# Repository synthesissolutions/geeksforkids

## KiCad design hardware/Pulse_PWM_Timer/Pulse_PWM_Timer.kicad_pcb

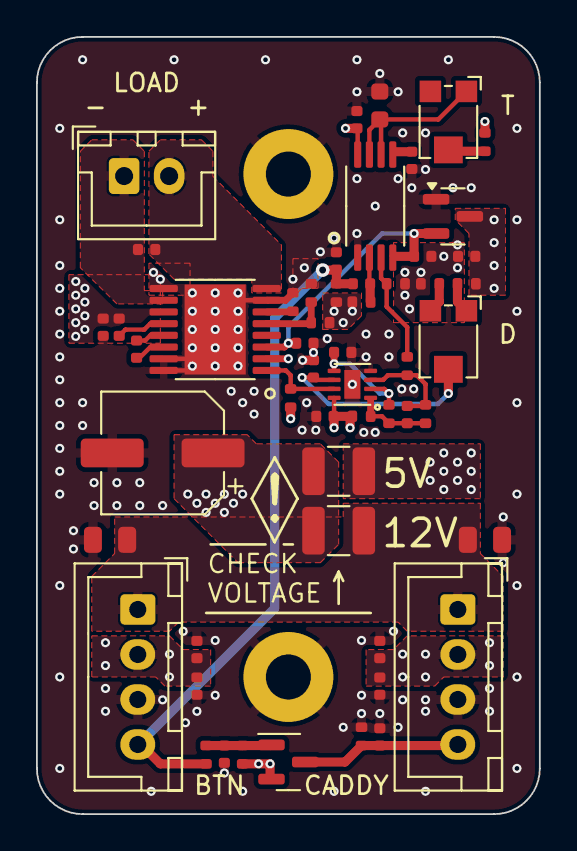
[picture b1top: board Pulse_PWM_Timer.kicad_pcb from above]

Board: 4 copper layers, 27.9 x 43.2 mm, 56 parts (0 on the bottom side), 27 nets.

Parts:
C1, C2, C3, C5, C9, C12, C16, C19, C21, C23, C25: 100nF; C_0402_1005Metric
C4, C10, C11, C17, C20: 10nF; C_0402_1005Metric
C6, C14: 22uF; C_0805_2012Metric
C7, C8, C15: 1uF; C_0402_1005Metric
C13: 10uF; C_0603_1608Metric
C18, C22: 22nF; C_0402_1005Metric
C24: 47uF; CP_Elec_6.3x5.4
F1, F2: 1.5A; Fuse_1210_3225Metric
H1, H2: MountingHole_Pad; MountingHole_2.5mm_Pad
J1: Action Input; JST_XH_B4B-XH-A_1x04_P2.50mm_Vertical
J2: Action Output; JST_XH_B4B-XH-A_1x04_P2.50mm_Vertical
J3: Load; JST_XH_B2B-XH-A_1x02_P2.50mm_Vertical
Q1: SI2301CDS-T1-GE3; SOT-23
R1, R17: 1k; R_0402_1005Metric
R2, R3, R4, R5, R6, R7, R8, R10: 100k; R_0402_1005Metric
R9, R11, R12, R13, R14: 10k; R_0402_1005Metric
R15: 20k; R_0402_1005Metric
R16: 27k; R_0402_1005Metric
RV1, RV2: 500k; Potentiometer_Bourns_TC33X_Vertical
U1: MAX809R; SOT-23
U2: NE555PWR; TSSOP-8_4.4x3mm_P0.65mm
U3: LM393QT; DFN-8-1EP_2x2mm_P0.5mm_EP0.9x1.6mm
U4: DRV8876PWPR; HTSSOP-16-1EP_4.4x5mm_P0.65mm_EP3.4x5mm_Mask2.46x2.31mm

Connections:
+5V: C1.1, C2.1, C7.1, C9.1, C12.1, C15.1, C16.1, F1.1, J1.2, J2.2, Q1.2 (S), R2.1, R3.1, R5.1, R7.1, R8.1, R13.1, R14.1, R15.1, U1.3 (VCC), U2.8 (VCC), U3.8 (V+), U4.2 (PH/IN2)
+12V: C6.1, C14.1, F2.1, J1.1, J2.1
+VM: C21.1, C23.2, C24.1, F1.2, F2.2, U4.11 (VM)
BTN_TRIG: C4.2, C8.1, J2.4, R1.1, R3.2
CADDY_TRIG: C5.2, J1.4, Q1.3 (D), R4.1
GND: C1.2, C2.2, C3.1, C4.1, C5.1, C6.2, C7.2, C9.2, C10.1, C11.1, C12.2, C13.2, C14.2, C15.2, C16.2, C17.2, C18.2, C20.1, C21.2, C24.2, H1.1, H2.1, J1.3, J2.3, R4.2, R6.2, R9.2, R16.2, R17.2, U1.1 (GND), U2.1 (GND), U3.4 (V-), U3.9, U4.7 (IMODE), U4.9 (PGND), U4.15 (GND), U4.16 (PMODE), U4.17 (PWRPAD)
unnamed: C19.2, R11.2, R12.1, R13.2, U3.1
unnamed: C25.1, J3.1, U4.10 (OUT2)
unnamed: C25.2, J3.2, U4.8 (OUT1)
unnamed: C3.2, Q1.1 (G), R1.2, R2.2
unnamed: R7.2, RV1.2
unnamed: R8.2, RV2.1
unnamed: R9.1, RV2.3
unnamed: C10.2, U2.5 (CV)
unnamed: C13.1, RV1.1, U2.6 (THR), U2.7 (DIS)
unnamed: C8.2, R5.2, U2.2 (TR)
unnamed: C19.1, R10.2, R11.1, U3.3 (+)
unnamed: C18.1, R12.2, U3.2 (-), U3.5 (+)
unnamed: C17.1, RV2.2, U3.6 (-)
unnamed: C22.2, U4.13 (CPH)
unnamed: C22.1, U4.14 (CPL)
unnamed: R17.1, U4.6 (IPROPRI)
unnamed: C23.1, U4.12 (VCP)
unnamed: R15.2, R16.1, U4.5 (VREF)
ON_DELAY: C11.2, C20.2, U1.2 (~RESET), U2.4 (R), U4.3 (nSLEEP)
PULSE_OUT: R6.1, R10.1, U2.3 (Q)
PWM_OUT: R14.2, U3.7, U4.1 (EN/IN1)

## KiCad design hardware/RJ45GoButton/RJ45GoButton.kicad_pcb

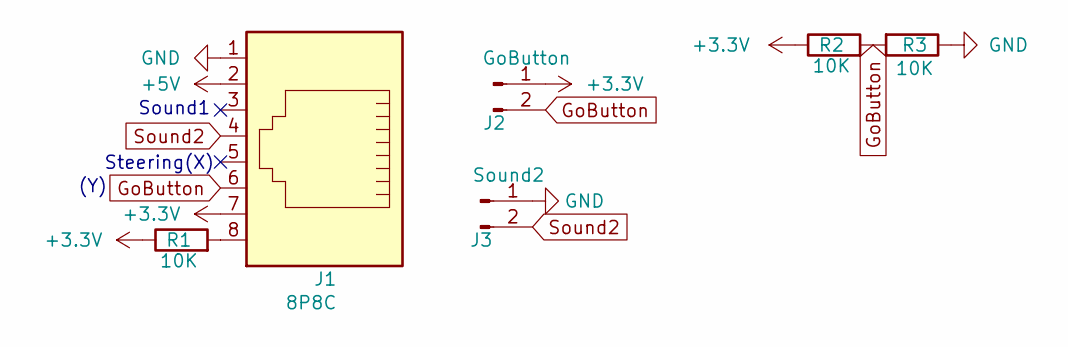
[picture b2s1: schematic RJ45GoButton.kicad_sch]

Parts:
J1: 8P8C; RJ45_x08_Tab_Up
J2: GoButton; JST_XH_B2B-XH-A_1x02_P2.50mm_Vertical
J3: Sound2; JST_XH_B2B-XH-A_1x02_P2.50mm_Vertical
R1, R2, R3: 10K; R_0805_2012Metric_Pad1.20x1.40mm_HandSolder

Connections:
+3.3V: J1.7, J2.1, R1.1, R2.1
+5V: J1.2
GND: J1.1, J3.1, R3.1
GoButton: J1.6, J2.2, R2.2, R3.2
unnamed: J1.8, R1.2
Sound2: J1.4, J3.2

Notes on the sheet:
Sound1
Steering(X)
(Y)

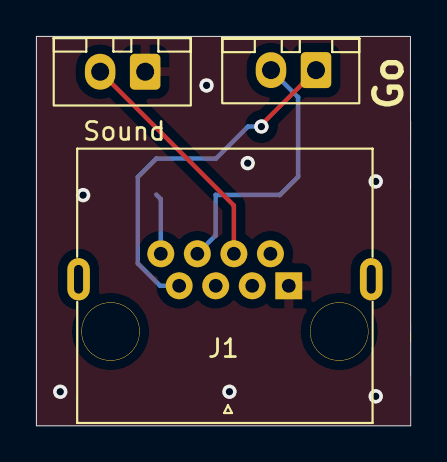
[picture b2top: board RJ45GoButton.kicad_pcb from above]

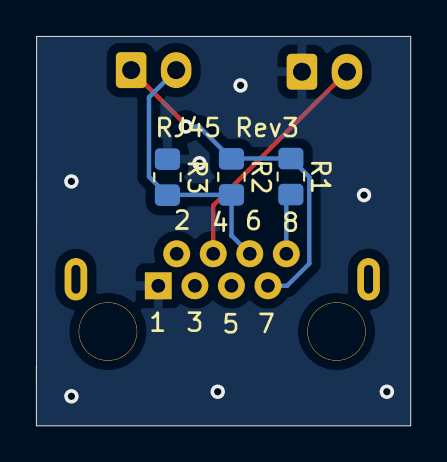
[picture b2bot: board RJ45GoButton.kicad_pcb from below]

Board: 2 copper layers, 20.8 x 21.6 mm, 6 parts (3 on the bottom side), 5 nets.

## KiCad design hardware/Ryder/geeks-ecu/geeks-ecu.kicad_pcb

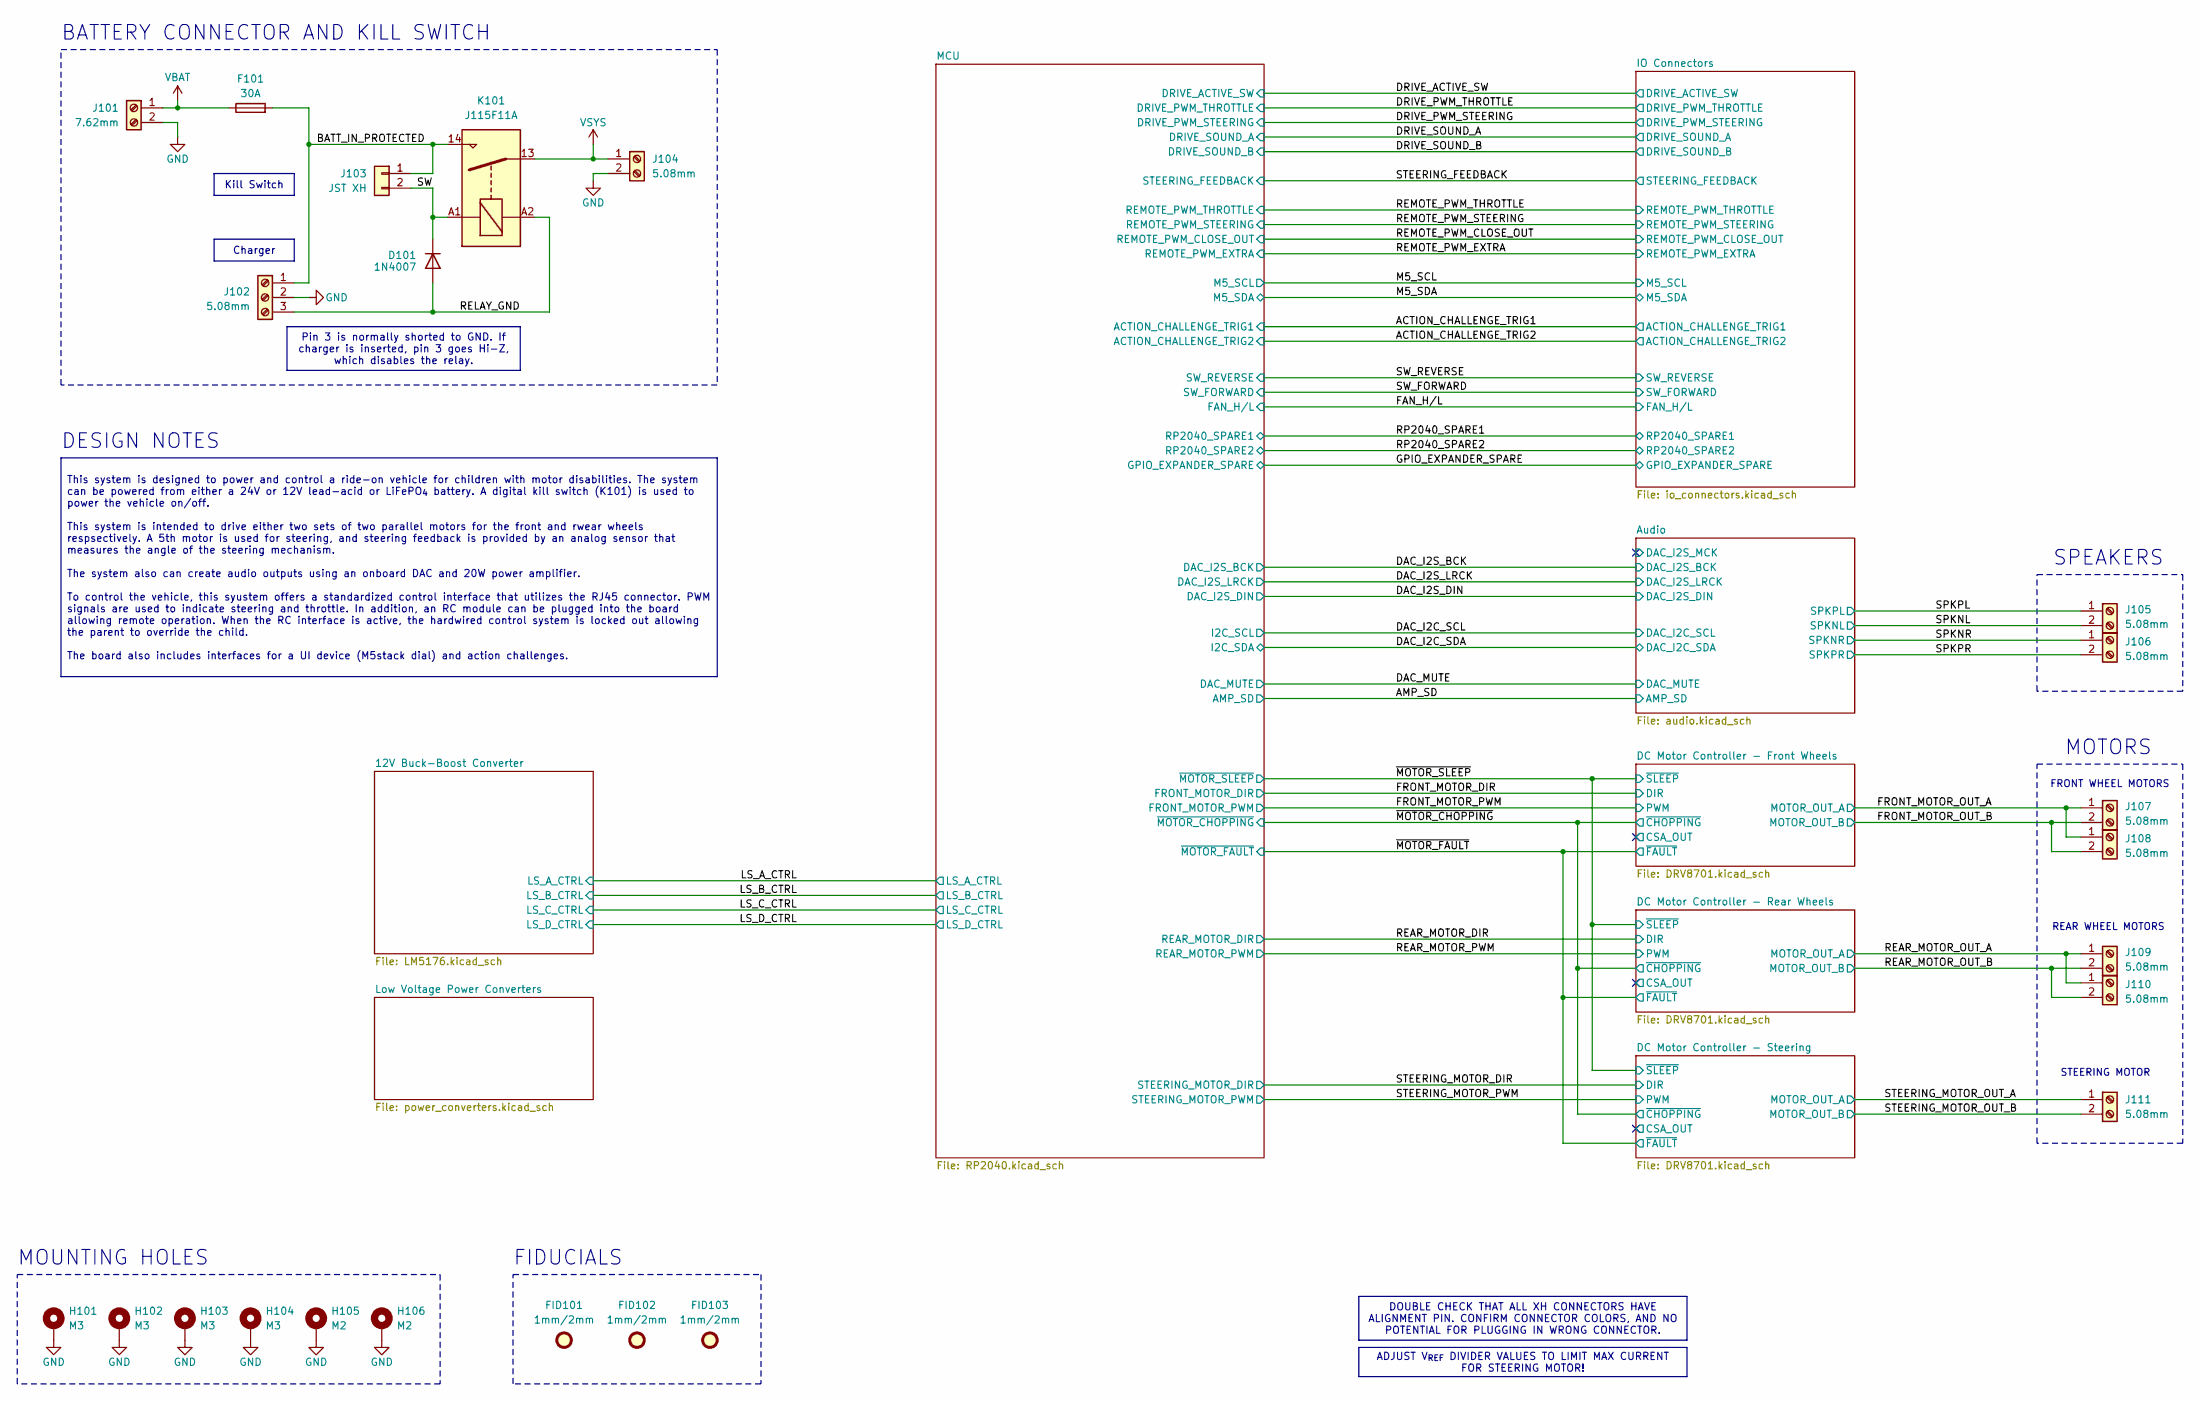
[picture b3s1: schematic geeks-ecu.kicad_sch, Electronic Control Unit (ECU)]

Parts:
D101: 1N4007; D_SOD-123F; MPN C64898
F101: 30A; Keystone_3568; MPN 3568
FID101, FID102, FID103: 1mm/2mm; Fiducial_1mm_Mask2mm
H101, H102, H103, H104: M3; MountingHole_3.2mm_M3_Pad_Via
H105, H106: M2; MountingHole_2.2mm_M2_Pad_Via
J101: 7.62mm; TerminalBlock_CUI_TB007-508-02_1x02_P5.08mm_Horizontal; MPN C5873515
J102: 5.08mm; TerminalBlock_CUI_TB007-508-03_1x03_P5.08mm_Horizontal; MPN C3820511
J103: JST XH; JST_XH_B2B-XH-AM_1x02_P2.50mm_Vertical; MPN C158012
J104, J105, J106, J107, J108, J109, J110, J111: 5.08mm; TerminalBlock_CUI_TB007-508-02_1x02_P5.08mm_Horizontal; MPN C3816270
K101: J115F11A; MPN J115F11A24VDCS6.9

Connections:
/BATT_IN_PROTECTED: F101.2, J102.1, J103.1, K101.14
/FRONT_MOTOR_OUT_A: J107.1, J108.1; also elsewhere on the board
/FRONT_MOTOR_OUT_B: J107.2, J108.2; also elsewhere on the board
/REAR_MOTOR_OUT_A: J109.1, J110.1; also elsewhere on the board
/REAR_MOTOR_OUT_B: J109.2, J110.2; also elsewhere on the board
/RELAY_GND: D101.2 (A), J102.3, K101.A2
/SPKNL: J105.2; also elsewhere on the board
/SPKNR: J106.1; also elsewhere on the board
/SPKPL: J105.1; also elsewhere on the board
/SPKPR: J106.2; also elsewhere on the board
/STEERING_MOTOR_OUT_A: J111.1; also elsewhere on the board
/STEERING_MOTOR_OUT_B: J111.2; also elsewhere on the board
/SW: D101.1 (K), J103.2, K101.A1
GND: H101.1, H102.1, H103.1, H104.1, H105.1, H106.1, J101.2, J102.2, J104.2; also elsewhere on the board
VBAT: F101.1, J101.1; also elsewhere on the board
VSYS: J104.1, K101.13; also elsewhere on the board

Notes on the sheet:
STEERING MOTOR
MOTORS
SPEAKERS
REAR WHEEL MOTORS
FIDUCIALS
FRONT WHEEL MOTORS
MOUNTING HOLES
DESIGN NOTES
BATTERY CONNECTOR AND KILL SWITCH
Charger
This system is designed to power and control a ride-on vehicle for children with motor disabilities. The system can be powered from either a 24V or 12V lead-acid or LiFePO_{4} battery. A digital kill switch (K101) is used to power the vehicle on/off. This system is intended to drive either two sets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
Pin 3 is normally shorted to GND. If charger is inserted, pin 3 goes Hi-Z, which disables the relay.
ADJUST V_{REF} DIVIDER VALUES TO LIMIT MAX CURRENT FOR STEERING MOTOR!
DOUBLE CHECK THAT ALL XH CONNECTORS HAVE ALIGNMENT PIN. CONFIRM CONNECTOR COLORS, AND NO POTENTIAL FOR PLUGGING IN WRONG CONNECTOR.
Kill Switch

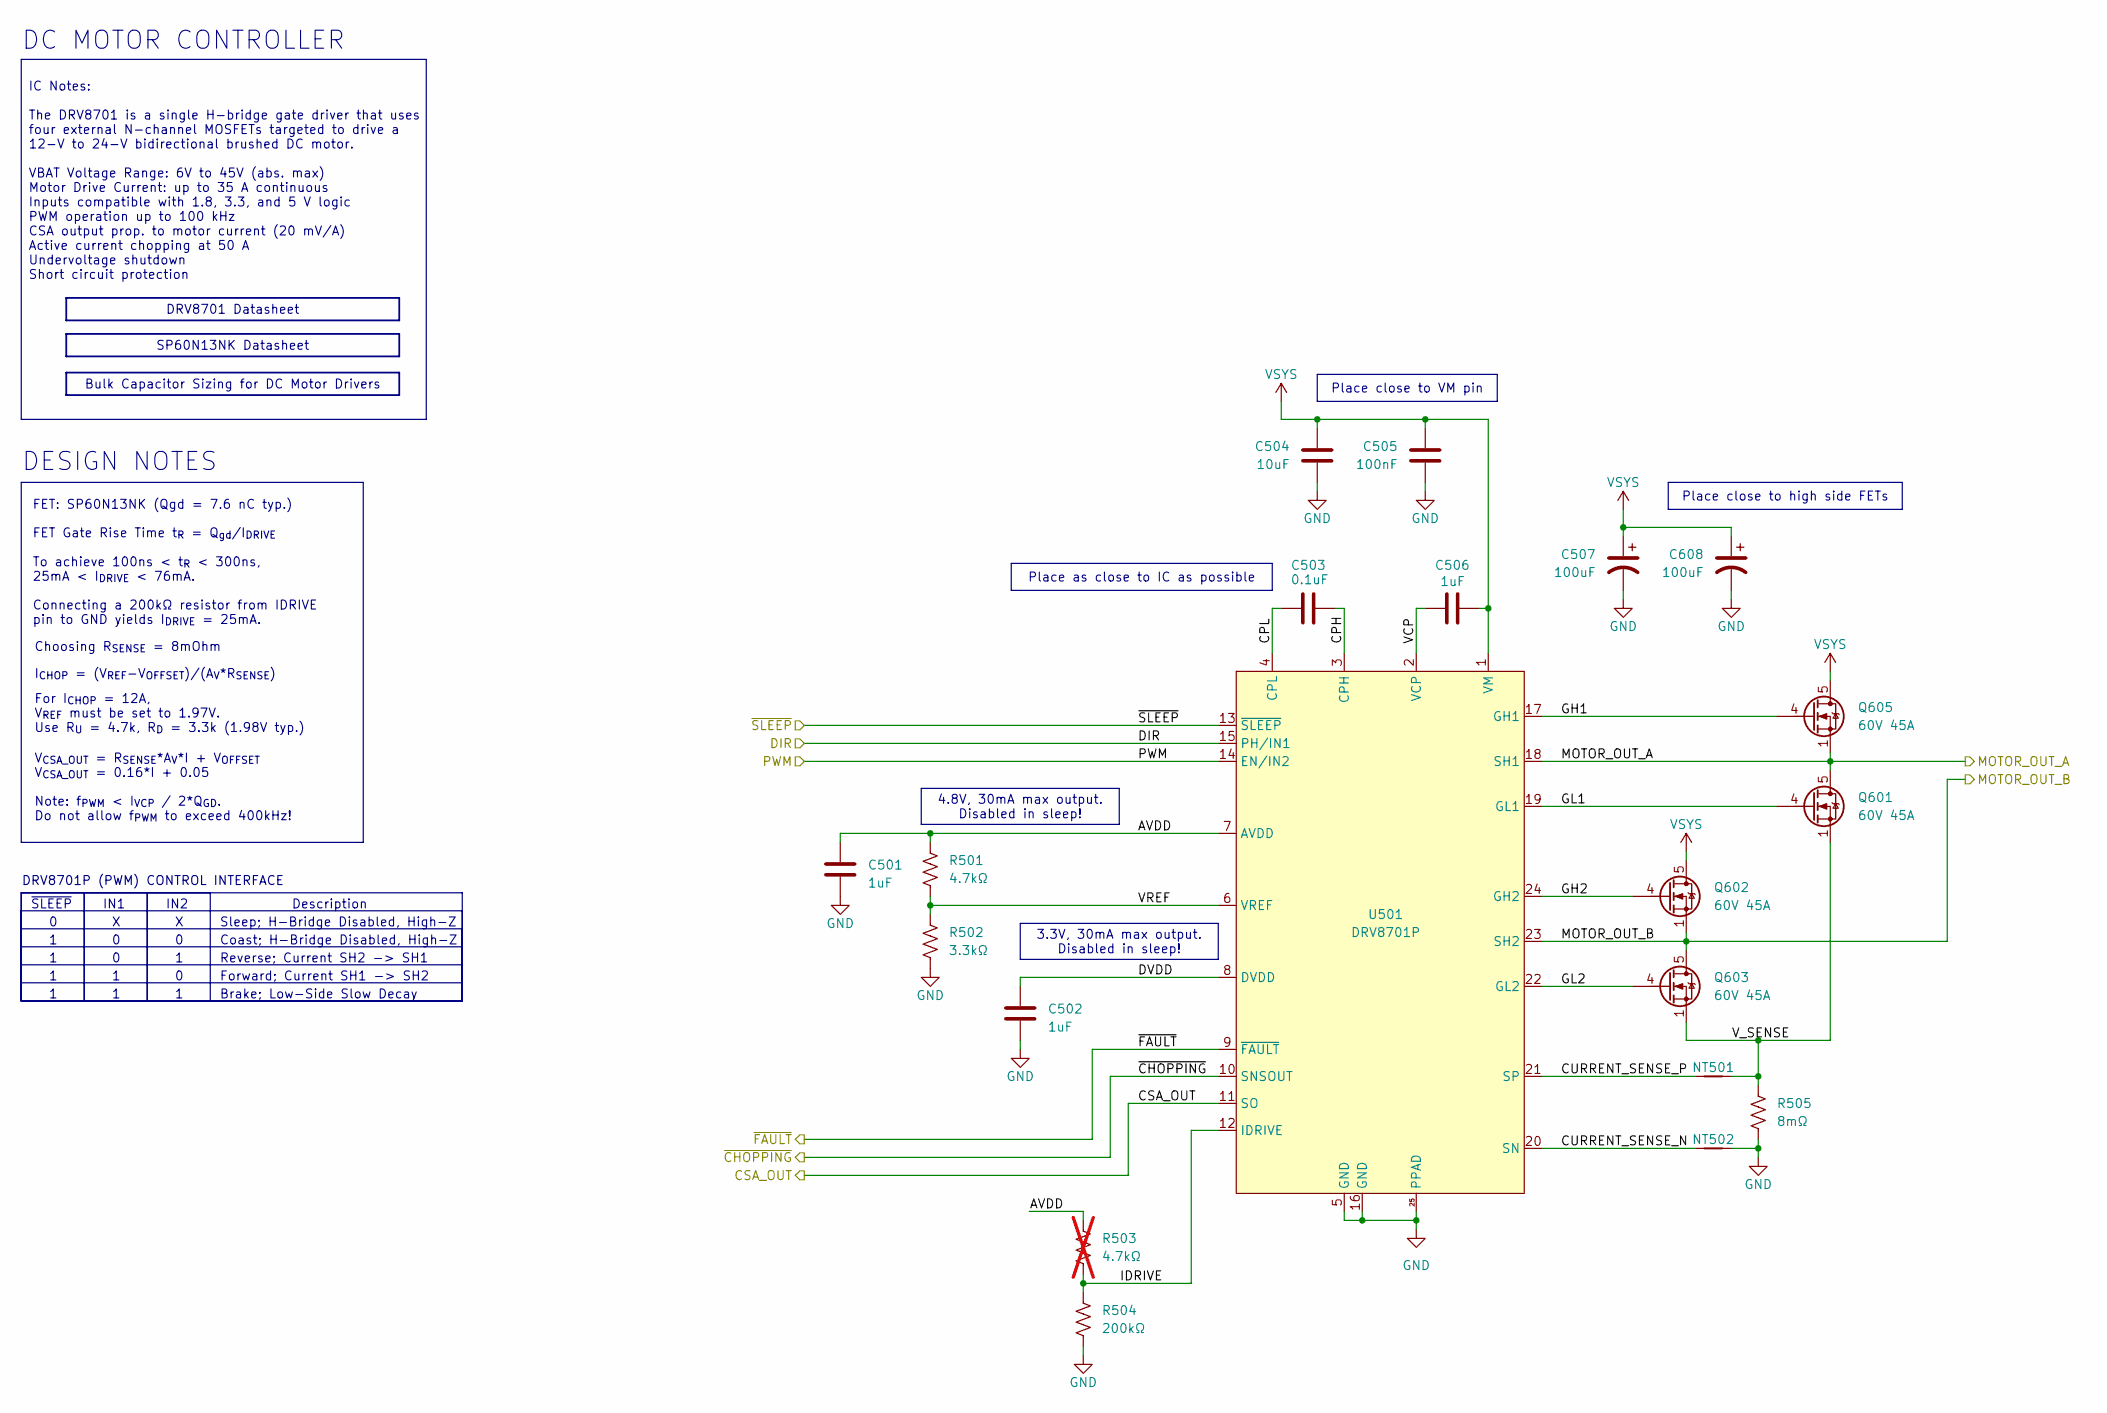
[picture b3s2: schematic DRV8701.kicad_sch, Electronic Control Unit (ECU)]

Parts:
C501, C502, C506: 1uF; C_0603_1608Metric; MPN C5199872
C503: 0.1uF; C_0603_1608Metric; MPN C14663
C504: 10uF; C_0805_2012Metric; MPN C2932476
C505: 100nF; C_0603_1608Metric; MPN C14663
C507, C608: 100uF; CP_Radial_D8.0mm_P3.50mm; MPN C106559
NT501, NT502: NetTie_2; NetTie-2_SMD_Pad0.5mm
Q601, Q602, Q603, Q605: 60V 45A; PQFN-8-EP_6x5mm_P1.27mm_Generic; MPN C41354975
R501: 4.7kΩ; R_0603_1608Metric; MPN C23162
R502: 3.3kΩ; R_0603_1608Metric; MPN C22978
R503: 4.7kΩ; R_0603_1608Metric; MPN C23162; not fitted
R504: 200kΩ; R_0603_1608Metric; MPN C25811
R505: 8mΩ; R_2512_6332Metric; MPN C509729
U501: DRV8701P; Texas_RGE0024H_VQFN-24-1EP_4x4mm_P0.5mm_EP2.7x2.7mm; MPN C114178

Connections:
/DC Motor Controller - Front Wheels/AVDD: C501.2, R501.1, R503.1, U501.7 (AVDD)
/DC Motor Controller - Front Wheels/CPH: C503.1, U501.3 (CPH)
/DC Motor Controller - Front Wheels/CPL: C503.2, U501.4 (CPL)
/DC Motor Controller - Front Wheels/CSA_OUT: U501.11 (SO)
/DC Motor Controller - Front Wheels/CURRENT_SENSE_N: NT502.1, U501.20 (SN)
/DC Motor Controller - Front Wheels/CURRENT_SENSE_P: NT501.2, U501.21 (SP)
/DC Motor Controller - Front Wheels/DVDD: C502.2, U501.8 (DVDD)
/DC Motor Controller - Front Wheels/GH1: Q605.4 (G), U501.17 (GH1)
/DC Motor Controller - Front Wheels/GH2: Q602.4 (G), U501.24 (GH2)
/DC Motor Controller - Front Wheels/GL1: Q601.4 (G), U501.19 (GL1)
/DC Motor Controller - Front Wheels/GL2: Q603.4 (G), U501.22 (GL2)
/DC Motor Controller - Front Wheels/IDRIVE: R503.2, R504.1, U501.12 (IDRIVE)
/DC Motor Controller - Front Wheels/VCP: C506.1, U501.2 (VCP)
/DC Motor Controller - Front Wheels/VREF: R501.2, R502.1, U501.6 (VREF)
/DC Motor Controller - Front Wheels/V_SENSE: NT501.1, Q601.1 (S), Q601.2 (S), Q601.3 (S), Q603.1 (S), Q603.2 (S), Q603.3 (S), R505.1
/FRONT_MOTOR_DIR: U501.15 (PH/IN1); also elsewhere on the board
/FRONT_MOTOR_OUT_A: Q601.5 (D), Q605.1 (S), Q605.2 (S), Q605.3 (S), U501.18 (SH1); also elsewhere on the board
/FRONT_MOTOR_OUT_B: Q602.1 (S), Q602.2 (S), Q602.3 (S), Q603.5 (D), U501.23 (SH2); also elsewhere on the board
/FRONT_MOTOR_PWM: U501.14 (EN/IN2); also elsewhere on the board
/~MOTOR_CHOPPING: U501.10 (SNSOUT); also elsewhere on the board
/~MOTOR_FAULT: U501.9 (~FAULT); also elsewhere on the board
/~MOTOR_SLEEP: U501.13 (~SLEEP); also elsewhere on the board
GND: C501.1, C502.1, C504.1, C505.2, C507.2, C608.2, NT502.2, R502.2, R504.2, R505.2, U501.5 (GND), U501.16 (GND), U501.25 (PPAD); also elsewhere on the board
VSYS: C504.2, C505.1, C506.2, C507.1, C608.1, Q602.5 (D), Q605.5 (D), U501.1 (VM); also elsewhere on the board

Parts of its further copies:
C601, C602, C606, C701, C702, C706: 1uF; C_0603_1608Metric; MPN C5199872
C603, C703: 0.1uF; C_0603_1608Metric; MPN C14663
C604, C704: 10uF; C_0805_2012Metric; MPN C2932476
C605, C705: 100nF; C_0603_1608Metric; MPN C14663
C607, C707, C708, C804: 100uF; CP_Radial_D8.0mm_P3.50mm; MPN C106559
NT601, NT602, NT701, NT702: NetTie_2; NetTie-2_SMD_Pad0.5mm
Q701, Q702, Q703, Q705, Q803, Q804, Q805, Q806: 60V 45A; PQFN-8-EP_6x5mm_P1.27mm_Generic; MPN C41354975
R601, R701: 4.7kΩ; R_0603_1608Metric; MPN C23162
R602, R702: 3.3kΩ; R_0603_1608Metric; MPN C22978
R603, R703: 4.7kΩ; R_0603_1608Metric; MPN C23162; not fitted
R604, R704: 200kΩ; R_0603_1608Metric; MPN C25811
R605, R705: 8mΩ; R_2512_6332Metric; MPN C509729
U601, U701: DRV8701P; Texas_RGE0024H_VQFN-24-1EP_4x4mm_P0.5mm_EP2.7x2.7mm; MPN C114178

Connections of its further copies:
/DC Motor Controller - Rear Wheels/AVDD: C601.2, R601.1, R603.1, U601.7 (AVDD)
/DC Motor Controller - Rear Wheels/CPH: C603.1, U601.3 (CPH)
/DC Motor Controller - Rear Wheels/CPL: C603.2, U601.4 (CPL)
/DC Motor Controller - Rear Wheels/CSA_OUT: U601.11 (SO)
/DC Motor Controller - Rear Wheels/CURRENT_SENSE_N: NT602.1, U601.20 (SN)
/DC Motor Controller - Rear Wheels/CURRENT_SENSE_P: NT601.2, U601.21 (SP)
/DC Motor Controller - Rear Wheels/DVDD: C602.2, U601.8 (DVDD)
/DC Motor Controller - Rear Wheels/GH1: Q705.4 (G), U601.17 (GH1)
/DC Motor Controller - Rear Wheels/GH2: Q702.4 (G), U601.24 (GH2)
/DC Motor Controller - Rear Wheels/GL1: Q701.4 (G), U601.19 (GL1)
/DC Motor Controller - Rear Wheels/GL2: Q703.4 (G), U601.22 (GL2)
/DC Motor Controller - Rear Wheels/IDRIVE: R603.2, R604.1, U601.12 (IDRIVE)
/DC Motor Controller - Rear Wheels/VCP: C606.1, U601.2 (VCP)
/DC Motor Controller - Rear Wheels/VREF: R601.2, R602.1, U601.6 (VREF)
/DC Motor Controller - Rear Wheels/V_SENSE: NT601.1, Q701.1 (S), Q701.2 (S), Q701.3 (S), Q703.1 (S), Q703.2 (S), Q703.3 (S), R605.1
/DC Motor Controller - Steering/AVDD: C701.2, R701.1, R703.1, U701.7 (AVDD)
/DC Motor Controller - Steering/CPH: C703.1, U701.3 (CPH)
/DC Motor Controller - Steering/CPL: C703.2, U701.4 (CPL)
/DC Motor Controller - Steering/CSA_OUT: U701.11 (SO)
/DC Motor Controller - Steering/CURRENT_SENSE_N: NT702.1, U701.20 (SN)
/DC Motor Controller - Steering/CURRENT_SENSE_P: NT701.2, U701.21 (SP)
/DC Motor Controller - Steering/DVDD: C702.2, U701.8 (DVDD)
/DC Motor Controller - Steering/GH1: Q803.4 (G), U701.17 (GH1)
/DC Motor Controller - Steering/GH2: Q805.4 (G), U701.24 (GH2)
/DC Motor Controller - Steering/GL1: Q804.4 (G), U701.19 (GL1)
/DC Motor Controller - Steering/GL2: Q806.4 (G), U701.22 (GL2)
/DC Motor Controller - Steering/IDRIVE: R703.2, R704.1, U701.12 (IDRIVE)
/DC Motor Controller - Steering/VCP: C706.1, U701.2 (VCP)
/DC Motor Controller - Steering/VREF: R701.2, R702.1, U701.6 (VREF)
/DC Motor Controller - Steering/V_SENSE: NT701.1, Q804.1 (S), Q804.2 (S), Q804.3 (S), Q806.1 (S), Q806.2 (S), Q806.3 (S), R705.1
/REAR_MOTOR_DIR: U601.15 (PH/IN1); also elsewhere on the board
/REAR_MOTOR_OUT_A: Q701.5 (D), Q705.1 (S), Q705.2 (S), Q705.3 (S), U601.18 (SH1); also elsewhere on the board
/REAR_MOTOR_OUT_B: Q702.1 (S), Q702.2 (S), Q702.3 (S), Q703.5 (D), U601.23 (SH2); also elsewhere on the board
/REAR_MOTOR_PWM: U601.14 (EN/IN2); also elsewhere on the board
/STEERING_MOTOR_DIR: U701.15 (PH/IN1); also elsewhere on the board
/STEERING_MOTOR_OUT_A: Q803.1 (S), Q803.2 (S), Q803.3 (S), Q804.5 (D), U701.18 (SH1); also elsewhere on the board
/STEERING_MOTOR_OUT_B: Q805.1 (S), Q805.2 (S), Q805.3 (S), Q806.5 (D), U701.23 (SH2); also elsewhere on the board
/STEERING_MOTOR_PWM: U701.14 (EN/IN2); also elsewhere on the board
/~MOTOR_CHOPPING: U601.10 (SNSOUT), U701.10 (SNSOUT); also elsewhere on the board
/~MOTOR_FAULT: U601.9 (~FAULT), U701.9 (~FAULT); also elsewhere on the board
/~MOTOR_SLEEP: U601.13 (~SLEEP), U701.13 (~SLEEP); also elsewhere on the board
GND: C601.1, C602.1, C604.1, C605.2, C607.2, C701.1, C702.1, C704.1, C705.2, C707.2, C708.2, C804.2, NT602.2, NT702.2, R602.2, R604.2, R605.2, R702.2, R704.2, R705.2, U601.5 (GND), U601.16 (GND), U601.25 (PPAD), U701.5 (GND), U701.16 (GND), U701.25 (PPAD); also elsewhere on the board
VSYS: C604.2, C605.1, C606.2, C607.1, C704.2, C705.1, C706.2, C707.1, C708.1, C804.1, Q702.5 (D), Q705.5 (D), Q803.5 (D), Q805.5 (D), U601.1 (VM), U701.1 (VM); also elsewhere on the board

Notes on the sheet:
Coast; H-Bridge Disabled, High-Z
DC MOTOR CONTROLLER
Choosing R_{SENSE} = 8mOhm
FET: SP60N13NK (Qgd = 7.6 nC typ.)
Sleep; H-Bridge Disabled, High-Z
Reverse; Current SH2 -> SH1
Description
FET Gate Rise Time t_{R} = Q_{gd}/I_{DRIVE} To achieve 100ns < t_{R} < 300ns, 25mA < I_{DRIVE} < 76mA.
For I_{CHOP} = 12A, V_{REF} must be set to 1.97V. Use R_{U} = 4.7k, R_{D} = 3.3k (1.98V typ.)
IN2
DESIGN NOTES
Forward; Current SH1 -> SH2
IN1
Brake; Low-Side Slow Decay
Note: f_{PWM} < I_{VCP} / 2*Q_{GD}. Do not allow f_{PWM} to exceed 400kHz!
I_{CHOP} = (V_{REF}-V_{OFFSET})/(A_{V}*R_{SENSE})
Connecting a 200kΩ resistor from IDRIVE pin to GND yields I_{DRIVE} = 25mA.
DRV8701P (PWM) CONTROL INTERFACE
V_{CSA_OUT} = R_{SENSE}*A_{V}*I + V_{OFFSET} V_{CSA_OUT} = 0.16*I + 0.05
~{SLEEP}
4.8V, 30mA max output. Disabled in sleep!
IC Notes: The DRV8701 is a single H-bridge gate driver that uses four external N-channel MOSFETs targeted to drive a 12-V to 24-V bidirectional brushed DC motor. VBAT Voltage Range: 6V to 45V (abs. max) Motor Drive Current: up to 35 A continuous Inputs compatible with 1.8, 3.3, and 5 V logic PWM op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
3.3V, 30mA max output. Disabled in sleep!
Place close to VM pin
SP60N13NK Datasheet
DRV8701 Datasheet
Bulk Capacitor Sizing for DC Motor Drivers
Place as close to IC as possible
Place close to high side FETs

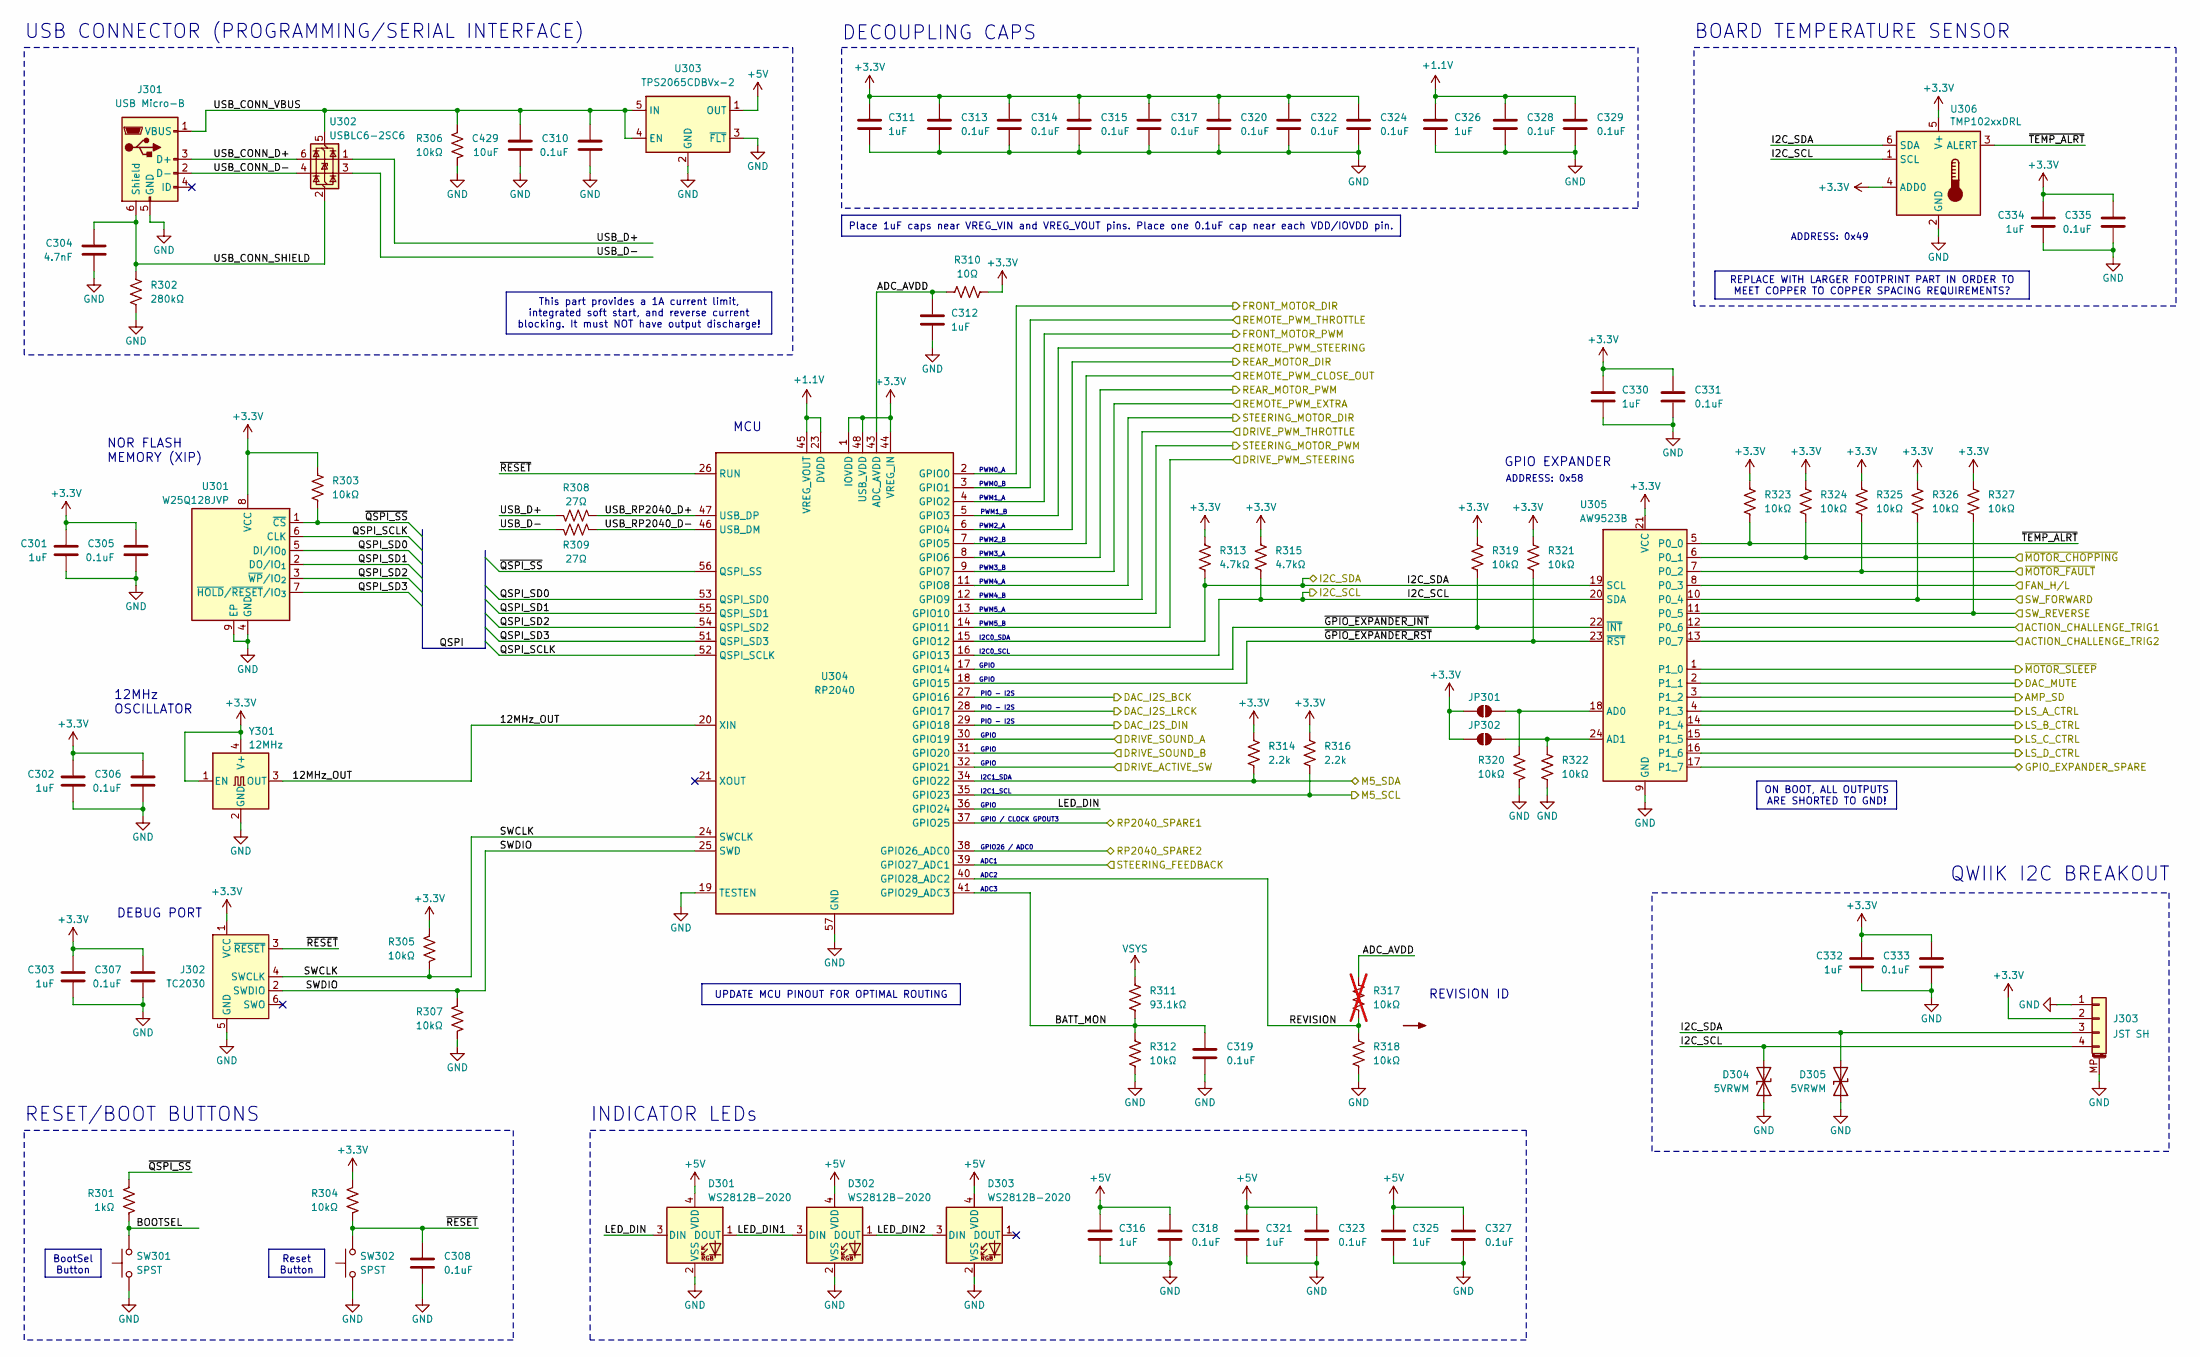
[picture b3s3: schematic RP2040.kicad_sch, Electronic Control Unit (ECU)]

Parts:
C301, C302, C303, C311, C312, C316, C321, C325, C326, C330, C332, C334: 1uF; C_0603_1608Metric; MPN C5199872
C304: 4.7nF; C_0805_2012Metric; MPN C565695
C305, C306, C307, C308, C310, C313, C314, C315, C317, C318, C319, C320, C322, C323, C324, C327, C328, C329, C331, C333, C335: 0.1uF; C_0603_1608Metric; MPN C14663
C429: 10uF; C_0805_2012Metric; MPN C2932476
D301, D302, D303: WS2812B-2020; LED_WS2812B-2020_PLCC4_2.0x2.0mm; MPN C965555
D304, D305: 5VRWM; D_SOD-882; MPN C110694
J301: USB Micro-B; USB_Micro-B_XKB_U254-051T-4BH83-F1S; MPN C397452
J302: TC2030; Tag-Connect_TC2030-IDC-NL_2x03_P1.27mm_Vertical
J303: JST SH; JST_SH_SM04B-SRSS-TB_1x04-1MP_P1.00mm_Horizontal
JP301, JP302: SolderJumper_2_Open; SolderJumper-2_P1.3mm_Open_RoundedPad1.0x1.5mm
R301: 1kΩ; R_0603_1608Metric; MPN C21190
R302: 280kΩ; R_0603_1608Metric; MPN C22970
R303, R304, R305, R306, R307, R312, R318, R319, R321, R323, R324, R325, R326, R327: 10kΩ; R_0603_1608Metric; MPN C25804
R308, R309: 27Ω; R_0603_1608Metric; MPN C25190
R310: 10Ω; R_0603_1608Metric; MPN C109318
R311: 93.1kΩ; R_0603_1608Metric; MPN C23266
R313, R315: 4.7kΩ; R_0603_1608Metric; MPN C23162
R314, R316: 2.2k; R_0603_1608Metric
R317: 10kΩ; R_0603_1608Metric; MPN C25804; not fitted
R320, R322: 10kΩ; R_0603_1608Metric; MPN C25804v
SW301, SW302: SPST; SW_SPST_TS-1088-xR020; MPN C720477
U301: W25Q128JVP; WSON-8-1EP_6x5mm_P1.27mm_EP3.4x4.3mm; MPN` C190862
U302: USBLC6-2SC6; SOT-23-6; MPN C7519
U303: TPS2065CDBVx-2; SOT-23-5
U304: RP2040; QFN-56-1EP_7x7mm_P0.4mm_EP3.2x3.2mm_ThermalVias
U305: AW9523B; QFN-24-1EP_4x4mm_P0.5mm_EP2.7x2.7mm; MPN C148077
U306: TMP102xxDRL; SOT-563; MPN C99269
Y301: 12MHz; Oscillator_SMD_EuroQuartz_XO32-4Pin_3.2x2.5mm; MPN C37635414

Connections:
+1.1V: C326.2, C328.1, C329.1, U304.23 (DVDD), U304.45 (VREG_VOUT), U304.50 (DVDD)
+5V: C316.2, C318.1, C321.2, C323.1, C325.2, C327.1, D301.4 (VDD), D302.4 (VDD), D303.4 (VDD), U303.1 (OUT); also elsewhere on the board
/ACTION_CHALLENGE_TRIG1: U305.12 (P0_6); also elsewhere on the board
/ACTION_CHALLENGE_TRIG2: U305.13 (P0_7); also elsewhere on the board
/AMP_SD: U305.3 (P1_2); also elsewhere on the board
/DAC_I2C_SCL: D304.2 (A2), J303.4, R315.2, U304.16 (GPIO13), U305.20 (SDA), U306.1 (SCL); also elsewhere on the board
/DAC_I2C_SDA: D305.2 (A2), J303.3, R313.2, U304.15 (GPIO12), U305.19 (SCL), U306.6 (SDA); also elsewhere on the board
/DAC_I2S_BCK: U304.27 (GPIO16); also elsewhere on the board
/DAC_I2S_DIN: U304.29 (GPIO18); also elsewhere on the board
/DAC_I2S_LRCK: U304.28 (GPIO17); also elsewhere on the board
/DAC_MUTE: U305.2 (P1_1); also elsewhere on the board
/DRIVE_ACTIVE_SW: U304.32 (GPIO21); also elsewhere on the board
/DRIVE_PWM_STEERING: U304.14 (GPIO11); also elsewhere on the board
/DRIVE_PWM_THROTTLE: U304.12 (GPIO9); also elsewhere on the board
/DRIVE_SOUND_A: U304.30 (GPIO19); also elsewhere on the board
/DRIVE_SOUND_B: U304.31 (GPIO20); also elsewhere on the board
/FAN_H/L: U305.8 (P0_3); also elsewhere on the board
/FRONT_MOTOR_DIR: U304.2 (GPIO0); also elsewhere on the board
/FRONT_MOTOR_PWM: U304.4 (GPIO2); also elsewhere on the board
/GPIO_EXPANDER_SPARE: U305.17 (P1_7); also elsewhere on the board
/LS_A_CTRL: U305.4 (P1_3); also elsewhere on the board
/LS_B_CTRL: U305.14 (P1_4); also elsewhere on the board
/LS_C_CTRL: U305.15 (P1_5); also elsewhere on the board
/LS_D_CTRL: U305.16 (P1_6); also elsewhere on the board
/M5_SCL: R316.2, U304.35 (GPIO23); also elsewhere on the board
/M5_SDA: R314.2, U304.34 (GPIO22); also elsewhere on the board
/MCU/12MHz_OUT: U304.20 (XIN), Y301.3 (OUT)
/MCU/ADC_AVDD: C312.2, R310.1, R317.1, U304.43 (ADC_AVDD)
/MCU/BATT_MON: C319.1, R311.2, R312.1, U304.41 (GPIO29_ADC3)
/MCU/BOOTSEL: R301.2, SW301.2
/MCU/LED_DIN: D301.3 (DIN), U304.36 (GPIO24)
/MCU/LED_DIN1: D301.1 (DOUT), D302.3 (DIN)
/MCU/LED_DIN2: D302.1 (DOUT), D303.3 (DIN)
/MCU/QSPI_SCLK: U301.6 (CLK), U304.52 (QSPI_SCLK)
/MCU/QSPI_SD0: U301.5 (DI/IO_{0}), U304.53 (QSPI_SD0)
/MCU/QSPI_SD1: U301.2 (DO/IO_{1}), U304.55 (QSPI_SD1)
/MCU/QSPI_SD2: U301.3 (~WP/IO_{2}), U304.54 (QSPI_SD2)
/MCU/QSPI_SD3: U301.7 (~HOLD/~RESET/IO_{3}), U304.51 (QSPI_SD3)
/MCU/REVISION: R317.2, R318.1, U304.40 (GPIO28_ADC2)
/MCU/SWCLK: J302.4 (SWCLK), R305.2, U304.24 (SWCLK)
/MCU/SWDIO: J302.2 (SWDIO), R307.1, U304.25 (SWD)
/MCU/USB_CONN_D+: J301.3 (D+), U302.6 (I/O1)
/MCU/USB_CONN_D-: J301.2 (D-), U302.4 (I/O2)
/MCU/USB_CONN_SHIELD: C304.1, J301.6 (Shield), R302.1, U302.2 (GND)
/MCU/USB_CONN_VBUS: C310.1, C429.2, J301.1 (VBUS), R306.1, U302.5 (VBUS), U303.4 (EN), U303.5 (IN)
/MCU/USB_D+: R308.2, U302.1 (I/O1)
/MCU/USB_D-: R309.2, U302.3 (I/O2)
/MCU/USB_RP2040_D+: R308.1, U304.47 (USB_DP)
/MCU/USB_RP2040_D-: R309.1, U304.46 (USB_DM)
/MCU/~GPIO_EXPANDER_INT: R319.2, U304.17 (GPIO14), U305.22 (~INT)
/MCU/~GPIO_EXPANDER_RST: R321.2, U304.18 (GPIO15), U305.23 (~RST)
/MCU/~QSPI_SS: R301.1, R303.2, U301.1 (~CS), U304.56 (QSPI_SS)
/MCU/~RESET: C308.1, J302.3 (~RESET), R304.2, SW302.2, U304.26 (RUN)
/MCU/~TEMP_ALRT: R323.2, U305.5 (P0_0), U306.3 (ALERT)
/REAR_MOTOR_DIR: U304.6 (GPIO4); also elsewhere on the board
/REAR_MOTOR_PWM: U304.8 (GPIO6); also elsewhere on the board
/REMOTE_PWM_CLOSE_OUT: U304.7 (GPIO5); also elsewhere on the board
/REMOTE_PWM_EXTRA: U304.9 (GPIO7); also elsewhere on the board
/REMOTE_PWM_STEERING: U304.5 (GPIO3); also elsewhere on the board
/REMOTE_PWM_THROTTLE: U304.3 (GPIO1); also elsewhere on the board
/RP2040_SPARE1: U304.37 (GPIO25); also elsewhere on the board
/RP2040_SPARE2: U304.38 (GPIO26_ADC0); also elsewhere on the board
/STEERING_FEEDBACK: U304.39 (GPIO27_ADC1); also elsewhere on the board
/STEERING_MOTOR_DIR: U304.11 (GPIO8); also elsewhere on the board
/STEERING_MOTOR_PWM: U304.13 (GPIO10); also elsewhere on the board
/SW_FORWARD: R326.2, U305.10 (P0_4); also elsewhere on the board
/SW_REVERSE: R327.2, U305.11 (P0_5); also elsewhere on the board
/~MOTOR_CHOPPING: R324.2, U305.6 (P0_1); also elsewhere on the board
/~MOTOR_FAULT: R325.2, U305.7 (P0_2); also elsewhere on the board
/~MOTOR_SLEEP: U305.1 (P1_0); also elsewhere on the board
GND: C301.1, C302.1, C303.1, C304.2, C305.2, C306.2, C307.2, C308.2, C310.2, C311.1, C312.1, C313.2, C314.2, C315.2, C316.1, C317.2, C318.2, C319.2, C320.2, C321.1, C322.2, C323.2, C324.2, C325.1, C326.1, C327.2, C328.2, C329.2, C330.1, C331.2, C332.1, C333.2, C334.1, C335.2, C429.1, D301.2 (VSS), D302.2 (VSS), D303.2 (VSS), D304.1 (A1), D305.1 (A1), J301.5 (GND), J302.5 (GND), J303.1, J303.MP (MountPin), R302.2, R306.2, R307.2, R312.2, R318.2, R320.2, R322.2, SW301.1, SW302.1, U301.4 (GND), U301.9 (EP), U303.2 (GND), U303.3 (~FLT), U304.19 (TESTEN), U304.57 (GND), U305.9 (GND), U305.25 (GND), U306.2 (GND), Y301.2 (GND); also elsewhere on the board
unnamed: JP301.2 (B), R320.1, U305.18 (AD0)
unnamed: JP302.2 (B), R322.1, U305.24 (AD1)
VSYS: R311.1; also elsewhere on the board

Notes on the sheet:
PWM4_B
ADDRESS: 0x58
PWM0_A
I2C1_SCL
ADC3
GPIO
PWM3_B
INDICATOR LEDs
GPIO / CLOCK GPOUT3
QWIIK I2C BREAKOUT
PWM2_A
MCU
PWM3_A
USB CONNECTOR (PROGRAMMING/SERIAL INTERFACE)
ADC1
ADC2
PIO - I2S
PWM5_A
REVISION ID
I2C0_SDA
DEBUG PORT
I2C0_SCL
PWM1_B
PWM4_A
PWM1_A
PWM5_B
I2C1_SDA
NOR FLASH MEMORY (XIP)
GPIO26 / ADC0
RESET/BOOT BUTTONS
ADDRESS: 0x49
GPIO EXPANDER
DECOUPLING CAPS
12MHz OSCILLATOR
BOARD TEMPERATURE SENSOR
PWM2_B
PWM0_B
UPDATE MCU PINOUT FOR OPTIMAL ROUTING
REPLACE WITH LARGER FOOTPRINT PART IN ORDER TO MEET COPPER TO COPPER SPACING REQUIREMENTS?
BootSel Button
